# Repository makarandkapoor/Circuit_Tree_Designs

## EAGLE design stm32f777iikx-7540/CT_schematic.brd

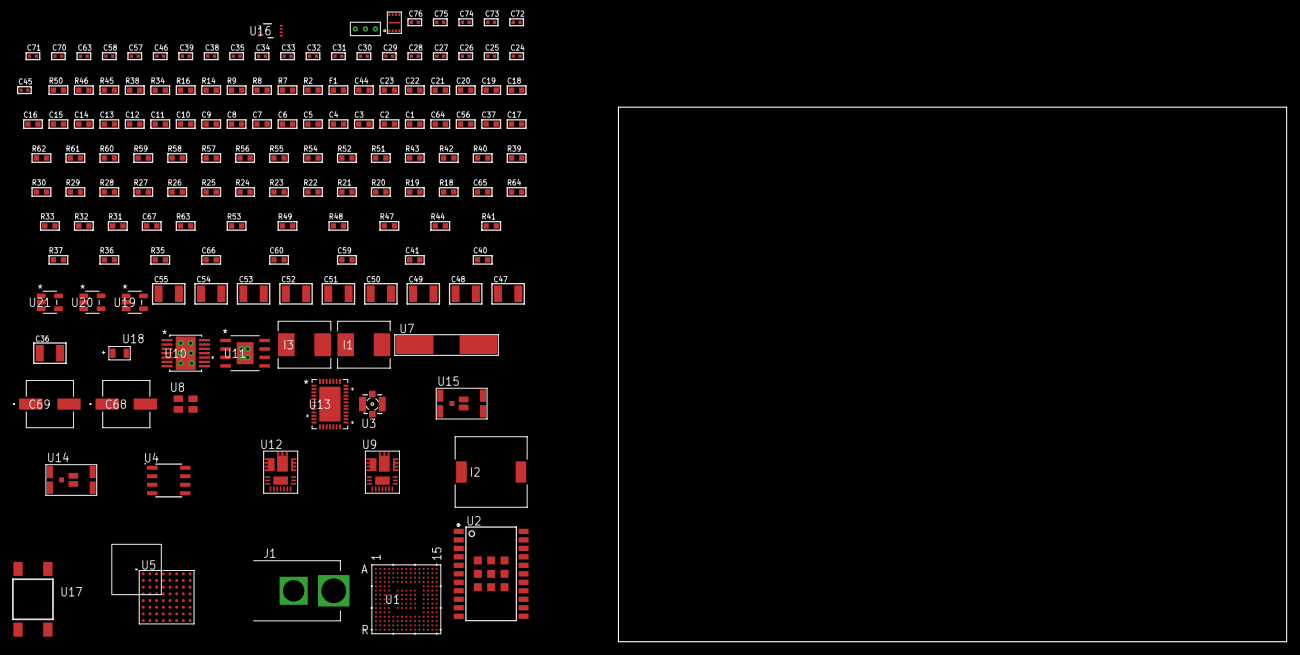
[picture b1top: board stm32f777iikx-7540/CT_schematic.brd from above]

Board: 2 copper layers, 100.0 x 80.0 mm, 152 parts (0 on the bottom side), 86 nets, no tracks yet.

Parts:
C1, C20, C44: 1e-06; C0603
C2, C3, C4, C5, C6, C7, C8, C9, C10, C11, C12, C13, C14, C15, C16, C18, C21, C22, C23: 1e-07; C0603
C17: 4.7e-06; C0603
C19: 1e-08; C0603
C24, C25: 1e-11; C0402
C26, C28, C30, C32, C34, C38, C39, C46, C57, C58, C63, C71, C73: 1e-07; C0402
C27, C29, C31, C33, C35, C70, C72, C74, C75, C76: 1e-08; C0402
C36, C55: 0.0001; C1210
C37, C56, C64: 2.2e-06; C0603
C40, C59: 8.6971073877236e-09; R0603
C41, C60: 2.9649229730876e-07; R0603
C45: 3.3e-09; C0402
C47, C48: 2.2e-05; C1210
C49, C50, C51, C52, C53, C54: 1e-05; C1210
C65: 2.45e-08; R0603
C66: 2.8258362168397e-09; R0603
C67: 7.105e-09; R0603
C68, C69: 0.0001; EXV-9H
F1: 240.0; L0603
I1, I3: 6.8e-07; IND25X25CZ
I2: 7e-06; DR1040
J1: PJ-037B; PJ-037B_PACKAGE
R2: 1000.0; R0603
R7, R8, R9: 4700.0; R0603
R14, R16, R45: 2200.0; R0603
R18, R19, R20, R21, R22, R23, R24, R25, R26, R27, R28, R29, R30, R54, R56, R57, R60, R61, R62: 10000.0; R0603
R31, R32, R33: 100000.0; R0603
R34, R46: 0.1; R0603
R35, R47: 4030.2416170974; R0603
R36, R48: 2878.7440122125; R0603
R37, R49: 58.613333333333; R0603
R38, R50: 130.0; R0603
R39, R51: 39000.0; R0603
R40, R52: 49900.0; R0603
R41, R53: 5147.5789473684; R0603
R42: 30000.0; R0603
R43: 22000.0; R0603
R44: 4031.5447154472; R0603
R55: 75000.0; R0603
R58, R59: 95300.0; R0603
R63: 139872.72727273; R0603
R64: 200000.0; R0603
U1: STM32F777IIK7; UFBGA176_25
U2: A2200-A
U3: 73412-0114; COAXIAL_C
U4: AT24C02D-SSHM-T; AT24C02D
U5: PC28F512P33BFD
U6: SST26WF080BT-104I/NP; USON-8
U7: ABLS-25.000MHZ-B2F-T
U8: ASEK-32.768KHz-ECST; ASEK
U9, U12: IR3899MTR1PBF
U10: tps54225PWP; HTSSOP14
U11: MIC5234YME; SOIC-8_EP
U13: LTC2928CUHF#PBF; QFN-38_UHF
U14, U15: IRF8306MTRPbF; IRF8306MTRPBF
U16: LSF0102DCTR; DCU0008A_N
U17: 4-1437565-2; SW_4-1437565-2
U18: Q65110A2395; LGM67K-G1J2-24-Z
U19, U20, U21: nc7sz125m5x; NC7SZ125M5X
U22: Dummy; DUMMY_PACKAGE_318

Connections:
CLK_CRYSTAL_U1_G1: C24.1, U1.G1, U7.1
CLK_CRYSTAL_U1_H1: C25.1, U1.H1, U7.2
CLK_U1_E1: U1.E1, U8.3
GND: C1.2, C2.2, C3.2, C4.2, C5.2, C6.2, C7.2, C8.2, C9.2, C10.2, C11.2, C12.2, C13.2, C14.2, C15.2, C16.2, C17.2, C18.2, C19.2, C20.2, C21.2, C22.2, C23.2, C24.2, C25.2, C26.2, C27.2, C28.2, C29.2, C30.2, C31.2, C32.2, C33.2, C34.2, C35.2, C37.2, C38.2, C39.2, C44.2, C45.2, C47.2, C48.2, C49.2, C50.2, C51.2, C52.2, C53.2, C54.2, C56.2, C57.2, C58.2, C63.2, C64.2, C65.2, C66.2, C67.2, C68.2, C69.2, C70.2, C71.2, C72.2, C73.2, C74.2, C75.2, C76.2, J1.2, R2.2, R18.2, R22.2, R24.2, R25.2, R34.1, R34.2, R36.2, R39.2, R41.2, R43.2, R45.2, R46.1, R46.2, R48.2, R51.2, R53.2, R55.2, R58.2, R59.2, R60.2, R61.2, R62.2, U1.D5, U1.D7, U1.D8, U1.D9, U1.F2, U1.F6, U1.F7, U1.F8, U1.F9, U1.F10, U1.F12, U1.G2, U1.G6, U1.G7, U1.G8, U1.G9, U1.G10, U1.G12, U1.H6, U1.H7, U1.H8, U1.H9, U1.H10, U1.H12, U1.J6, U1.J7, U1.J8, U1.J9, U1.J10, U1.K6, U1.K7, U1.K8, U1.K9, U1.K10, U1.M1, U1.M8, U1.M9, U1.N1, U2.7, U2.8, U2.23, U2.24, U2.25, U2.26, U2.27, U2.28, U2.29, U2.30, U2.31, U4.4, U5.B2, U5.H2, U5.H4, U5.H6, U6.4, U6.9, U8.2, U9.4, U9.11, U9.17, U10.5, U10.8, U10.9, U10.15, U11.7, U11.EPAD, U12.4, U12.11, U12.17, U13.8, U13.9, U13.10, U13.12, U13.13, U13.24, U13.25, U13.30, U13.32, U13.39, U16.1, U18.C, U19.1, U19.3, U20.1, U20.3, U21.1, U21.3, U22.1
NET_U1_C6: R19.1, U1.C6
NET_U1_D6: R18.1, U1.D6
NET_U1_F13: C23.1, U1.F13
NET_U1_H4: R14.1, U1.H4, U4.6
NET_U1_J1: R9.1, U1.J1, U21.4
NET_U1_J4: R16.1, U1.J4, U4.5
NET_U1_L4: R20.1, U1.L4
NET_U1_R1: C19.1, C20.1, F1.1, U1.P1, U1.R1
NET_U1_R15: U17.3, U17.4
NET_U2_2: R21.2, U2.2
NET_U2_17: R21.1, U2.17
NET_U2_22: R8.1, U2.22, U20.4
NET_U3_1: U2.11, U3.1
NET_U3_2: U2.10, U3.2, U3.3, U3.4
NET_U4_1: R23.1, U4.1
NET_U4_2: R24.1, U4.2
NET_U4_3: R25.1, U4.3
NET_U4_7: R22.1, U4.7
NET_U5_A4: C32.1, C33.1, U5.A4
NET_U5_B4: R27.1, U5.B4
NET_U5_C6: R29.1, U5.C6
NET_U5_D4: R7.1, U5.D4, U19.4
NET_U5_F6: R26.1, U5.F6
NET_U5_F8: R28.1, U5.F8
NET_U5_G8: R30.1, U5.G8
NET_U9_1: C40.1, R35.1, R36.1, R37.1, R38.1, U9.1, U9.8
NET_U9_2: C39.1, U9.2
NET_U9_3: C40.2, C41.1, C41.2, U9.3
NET_U9_5: R39.1, U9.5
NET_U9_10: C37.1, U9.10
NET_U9_12: C36.1, I1.1, U9.12
NET_U9_14: C36.2, U9.14
NET_U9_15: R40.1, R41.1, U9.15
NET_U9_ATNET_3: I1.2, R35.2
NET_U9_ATNET_4: C41.2, R37.2
NET_U10_2: R42.2, R43.1, U10.2
NET_U10_3: C44.1, U10.3
NET_U10_4: C45.1, U10.4
NET_U10_10: C46.1, I2.1, U10.10, U10.11
NET_U10_12: C46.2, U10.12
NET_U11_4: R44.2, R45.1, U11.4
NET_U12_1: C59.1, R47.1, R48.1, R49.1, R50.1, U12.1, U12.8
NET_U12_2: C58.1, U12.2
NET_U12_3: C59.2, C60.1, C60.2, U12.3
NET_U12_5: R51.1, U12.5
NET_U12_10: C56.1, U12.10
NET_U12_12: C55.1, I3.1, U12.12
NET_U12_14: C55.2, U12.14
NET_U12_15: R52.1, R53.1, U12.15
NET_U12_ATNET_3: I3.2, R47.2
NET_U12_ATNET_4: C60.2, R49.2
NET_U13_3: R61.1, U13.3
NET_U13_6: R58.1, U13.6
NET_U13_7: R59.1, U13.7
NET_U13_16: R60.1, R63.1, U13.16
NET_U13_18: R57.1, U13.18
NET_U13_19: R56.1, U13.19, U13.20
NET_U13_21: R54.1, R55.1, U13.21, U19.2, U20.2, U21.2
NET_U13_26: C66.1, U13.26
NET_U13_27: C65.1, U13.27
NET_U13_28: C67.1, U13.28
NET_U13_38: R62.1, U13.38
NET_U14_3: U13.2, U14.3
NET_U15_3: U13.37, U15.3
NET_U16_8: R64.1, U16.8
NET_U17_1: R2.1, U17.1, U17.2
PROC_I2C1_SCL_TOXCVR: U2.15, U16.5
PROC_I2C1_SDA_TOXCVR: U2.16, U16.6
PROC_PE2: U1.A2, U22.3
PROC_PE3: U1.A1, U22.2
PROC_QUADSPI_BK1_IO0: U1.F14, U6.5
PROC_QUADSPI_BK1_IO1: U1.B14, U6.2
PROC_QUADSPI_BK1_IO2: R32.1, U1.K1, U6.3
PROC_QUADSPI_BK1_IO3: R33.1, U1.K2, U6.7
PROC_QUADSPI_BK1_NCS: R31.1, U1.B6, U6.1
PROC_QUADSPI_CLK: U1.L1, U6.6
VCC_16V8: C63.1, C64.1, C68.1, C69.1, J1.1, R54.2, R56.2, R57.2, R63.2, U13.11, U13.22, U14.1, U14.2, U14.6, U14.7, U15.1, U15.2, U15.6, U15.7
VCC_S1_16V8: C38.1, C49.1, C50.1, C51.1, C52.1, R40.2, U9.9, U10.7, U10.13, U10.14, U11.5, U11.8, U14.4, U14.5
VCC_S2_16V8: C57.1, R52.2, U12.9, U15.4, U15.5
VCC_TIER1_1V2: C22.1, I1.2, R35.2, U1.M10
VCC_TIER1_1V8: C1.1, C2.1, C3.1, C4.1, C5.1, C6.1, C7.1, C8.1, C9.1, C10.1, C11.1, C12.1, C13.1, C14.1, C15.1, C16.1, C17.1, C18.1, C27.1, C34.1, C47.1, C48.1, C72.1, C73.1, C74.1, C75.1, C76.1, F1.2, I2.2, R9.2, R14.2, R16.2, R19.2, R20.2, R23.2, R31.2, R32.2, R33.2, R42.1, U1.C1, U1.C5, U1.C7, U1.C8, U1.C9, U1.F3, U1.G3, U1.G13, U1.J12, U1.J13, U1.K4, U1.N8, U1.N9, U1.N10, U4.8, U6.8, U10.1, U16.2, U19.5, U20.5, U21.5
VCC_TIER1_3V3: C21.1, C26.1, C28.1, C29.1, C30.1, C31.1, C35.1, C53.1, C54.1, C70.1, C71.1, R7.2, R8.2, R26.2, R27.2, R28.2, R29.2, R30.2, R44.1, R64.2, U1.H13, U2.20, U5.A6, U5.D5, U5.D6, U5.G4, U5.H3, U8.4, U11.1, U16.7
VCC_TIER2_1V2: I3.2, R47.2

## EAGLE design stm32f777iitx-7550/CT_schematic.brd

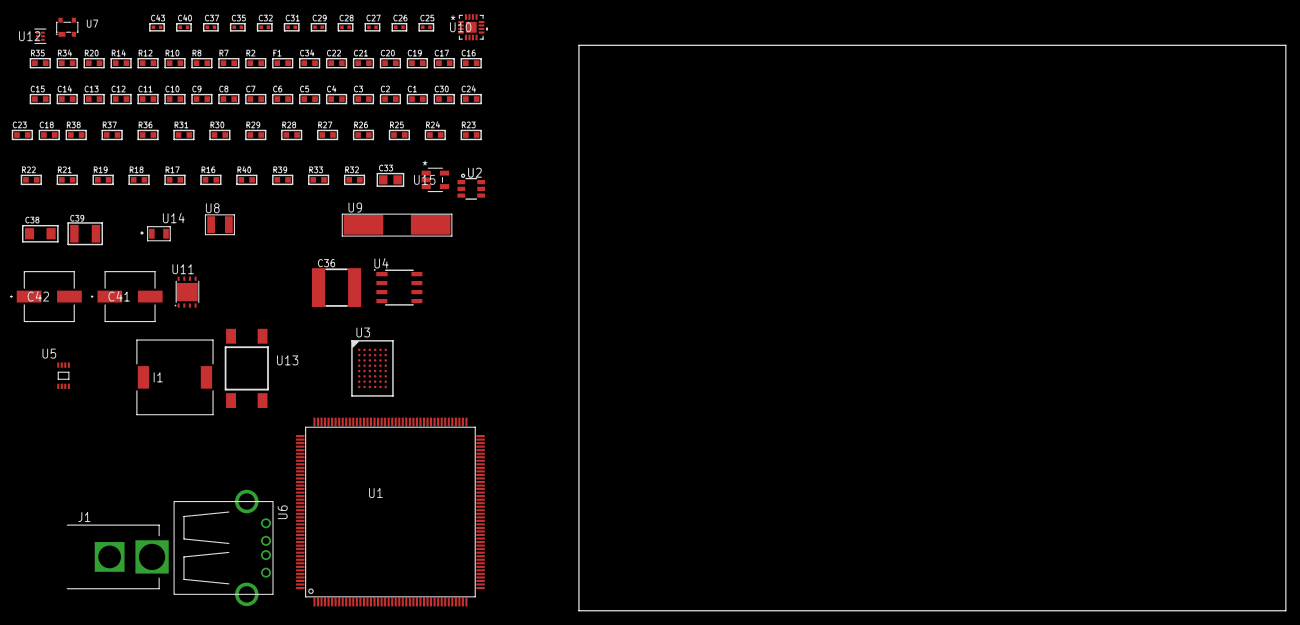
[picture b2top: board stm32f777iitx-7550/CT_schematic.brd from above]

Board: 2 copper layers, 100.0 x 80.0 mm, 92 parts (0 on the bottom side), 82 nets, no tracks yet.

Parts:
C1, C21, C34: 1e-06; C0603
C2, C3, C4, C5, C6, C7, C8, C9, C10, C11, C12, C13, C14, C15, C16, C17, C19, C22: 1e-07; C0603
C18: 4.7e-06; C0603
C20: 1e-08; C0603
C23, C24, C30: 2.2e-06; C0603
C25, C26, C27, C28: 1e-11; C0402
C29, C35, C40: 1e-07; C0402
C31, C32, C37, C43: 1e-08; C0402
C33: 1e-05; C0805
C36: 6.8e-05; 2220
C38: 1e-05; C1206
C39: 1e-05; C1210
C41, C42: 0.0001; EXV-9H
F1: 240.0; L0603
I1: 3.8e-06; DR1040
J1: PJ-037B; PJ-037B_PACKAGE
R2, R35: 1000.0; R0603
R7: 4700.0; R0603
R8, R10, R12, R14: 2200.0; R0603
R16: 47000.0; R0603
R17, R18, R19, R21, R22, R23, R24, R25, R26, R27, R28, R29, R36, R37: 10000.0; R0603
R20: 1270.0; R0603
R30: 20000.0; R0603
R31: 62000.0; R0603
R32: 300000.0; R0603
R33: 100000.0; R0603
R34: 3900.0; R0603
R38: 18000.0; R0603
R39: 470000.0; R0603
R40: 120000.0; R0603
U1: STM32F777IIT6; LQFP176
U2: MAX4995AAUT+T; SOT-23-6
U3: CY62147GE30-45BVXI; VFBGA48
U4: AT24C02D-SSHM-T; AT24C02D
U5: 24AA01T-I/MNY; TDFN-8/6MM
U6: 61400416021; USB-A-H
U7: prtr5v0u2ax; SOT143B
U8: ABS07-32.768KHZ-7-T
U9: ABLS-25.000MHZ-B2F-T
U10: LTC3601EUD#PBF; QFN-16_EP
U11: LP3878SDX-ADJ/NOPB; WSON-8
U12: TPS3895ADRYR; SON-6
U13: 4-1437565-2; SW_4-1437565-2
U14: Q65110A2395; LGM67K-G1J2-24-Z
U15: nc7sz125m5x; NC7SZ125M5X

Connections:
CLK_CRYSTAL_U1_9: C25.1, U1.9, U8.1
CLK_CRYSTAL_U1_10: C26.1, U1.10, U8.2
CLK_CRYSTAL_U1_29: C27.1, U1.29, U9.1
CLK_CRYSTAL_U1_30: C28.1, U1.30, U9.2
GND: C1.2, C2.2, C3.2, C4.2, C5.2, C6.2, C7.2, C8.2, C9.2, C10.2, C11.2, C12.2, C13.2, C14.2, C15.2, C16.2, C17.2, C18.2, C19.2, C20.2, C21.2, C22.2, C23.2, C24.2, C25.2, C26.2, C27.2, C28.2, C29.2, C30.2, C31.2, C32.2, C33.2, C34.2, C36.1, C36.2, C37.2, C38.2, C39.2, C40.2, C41.2, C42.2, C43.2, J1.2, R2.2, R16.2, R17.2, R19.2, R20.2, R22.2, R26.2, R28.2, R29.2, R30.2, R32.2, R35.2, R38.2, R40.2, U1.14, U1.22, U1.37, U1.61, U1.71, U1.90, U1.102, U1.113, U1.126, U1.135, U1.148, U1.158, U2.2, U3.D1, U3.E6, U4.4, U5.4, U6.4, U6.5, U6.6, U7.1, U10.1, U10.9, U10.17, U11.3, U11.PAD, U12.2, U14.C, U15.1, U15.3
NET_U1_31: R7.1, U1.31, U15.4
NET_U1_39: C20.1, C21.1, F1.1, U1.38, U1.39
NET_U1_45: R12.1, U1.45, U5.6
NET_U1_46: R14.1, U1.46, U5.5
NET_U1_48: R19.1, U1.48
NET_U1_81: C23.1, U1.81
NET_U1_121: R20.1, U1.121
NET_U1_125: C24.1, U1.125
NET_U1_164: R8.1, U1.164, U4.6
NET_U1_165: R10.1, U1.165, U4.5
NET_U1_166: R17.1, U1.166
NET_U1_171: R18.1, U1.171
NET_U1_176: U13.3, U13.4
NET_U2_3: R16.1, U2.3
NET_U4_1: R27.1, U4.1
NET_U4_2: R28.1, U4.2
NET_U4_3: R29.1, U4.3
NET_U4_7: R26.1, U4.7
NET_U10_3: C35.2, I1.1, U10.3, U10.4
NET_U10_6: C35.1, U10.6
NET_U10_7: C34.1, U10.7, U10.12
NET_U10_10: R32.1, U10.10
NET_U10_11: R30.1, R31.1, U10.11
NET_U10_ATNET_3: I1.2, R31.2
NET_U11_1: C37.1, U11.1
NET_U11_6: R34.2, R35.1, U11.6
NET_U11_8: R33.1, U11.8
NET_U12_1: R37.1, R38.1, U12.1
NET_U12_3: R39.2, R40.1, U12.3
NET_U12_4: R36.1, U12.4, U15.2
NET_U13_1: R2.1, U13.1, U13.2
PROC_FMC_A0: U1.16, U3.A3
PROC_FMC_A1: U1.17, U3.A4
PROC_FMC_A2: U1.18, U3.A5
PROC_FMC_A3: U1.19, U3.B3
PROC_FMC_A4: U1.20, U3.B4
PROC_FMC_A5: U1.21, U3.C3
PROC_FMC_A6: U1.60, U3.C4
PROC_FMC_A7: U1.63, U3.D4
PROC_FMC_A8: U1.64, U3.H2
PROC_FMC_A9: U1.65, U3.H3
PROC_FMC_A10: U1.66, U3.H4
PROC_FMC_A11: U1.67, U3.H5
PROC_FMC_A12: U1.106, U3.G3
PROC_FMC_A13: U1.107, U3.G4
PROC_FMC_A14: U1.108, U3.F3
PROC_FMC_A15: U1.109, U3.F4
PROC_FMC_A16: U1.99, U3.E4
PROC_FMC_A17: U1.100, U3.D3
PROC_FMC_D0: U1.104, U3.B6
PROC_FMC_D1: U1.105, U3.C5
PROC_FMC_D2: U1.142, U3.C6
PROC_FMC_D3: U1.143, U3.D5
PROC_FMC_D4: U1.68, U3.E5
PROC_FMC_D5: U1.69, U3.F5
PROC_FMC_D6: U1.70, U3.F6
PROC_FMC_D7: U1.73, U3.G6
PROC_FMC_D8: U1.74, U3.B1
PROC_FMC_D9: U1.75, U3.C1
PROC_FMC_D10: U1.76, U3.C2
PROC_FMC_D11: U1.77, U3.D2
PROC_FMC_D12: U1.78, U3.E2
PROC_FMC_D13: U1.96, U3.F2
PROC_FMC_D14: U1.97, U3.F1
PROC_FMC_D15: U1.98, U3.G1
PROC_FMC_NBL0: U1.169, U3.A1
PROC_FMC_NE2: R24.1, U1.117, U3.B5
PROC_FMC_NOE: R23.1, U1.146, U3.A2
PROC_FMC_NWE: R25.1, U1.147, U3.G5
PROC_GPIO_TO_U1_USB_FAULT: R21.1, U1.2, U2.6
PROC_GPIO_TO_U1_VBUS_EN: R22.1, U1.1, U2.4
PROC_USB_OTG_FS_DM: U1.122, U6.2, U7.3
PROC_USB_OTG_FS_DP: U1.123, U6.3, U7.2
PROC_USB_OTG_FS_VBUS: U1.120, U2.1, U6.1, U7.4
VCC_S1_10V1: C33.1, C38.1, C41.1, C42.1, J1.1, R33.2, U10.15, U10.16, U11.4
VCC_TIER1_2V5: C1.1, C2.1, C3.1, C4.1, C5.1, C6.1, C7.1, C8.1, C9.1, C10.1, C11.1, C12.1, C13.1, C14.1, C15.1, C16.1, C17.1, C18.1, C19.1, C22.1, C29.1, C30.1, C31.1, C32.1, C36.2, C40.1, C43.1, F1.2, I1.2, R7.2, R8.2, R10.2, R12.2, R14.2, R18.2, R21.2, R23.2, R24.2, R25.2, R27.2, R31.2, R36.2, R37.2, R39.1, U1.6, U1.15, U1.23, U1.36, U1.49, U1.62, U1.72, U1.82, U1.91, U1.103, U1.114, U1.127, U1.136, U1.149, U1.159, U1.172, U3.D6, U3.E1, U4.8, U5.7, U5.8, U10.8, U12.6, U15.5
VCC_TIER1_5V0: C39.1, R34.1, U2.5, U11.5

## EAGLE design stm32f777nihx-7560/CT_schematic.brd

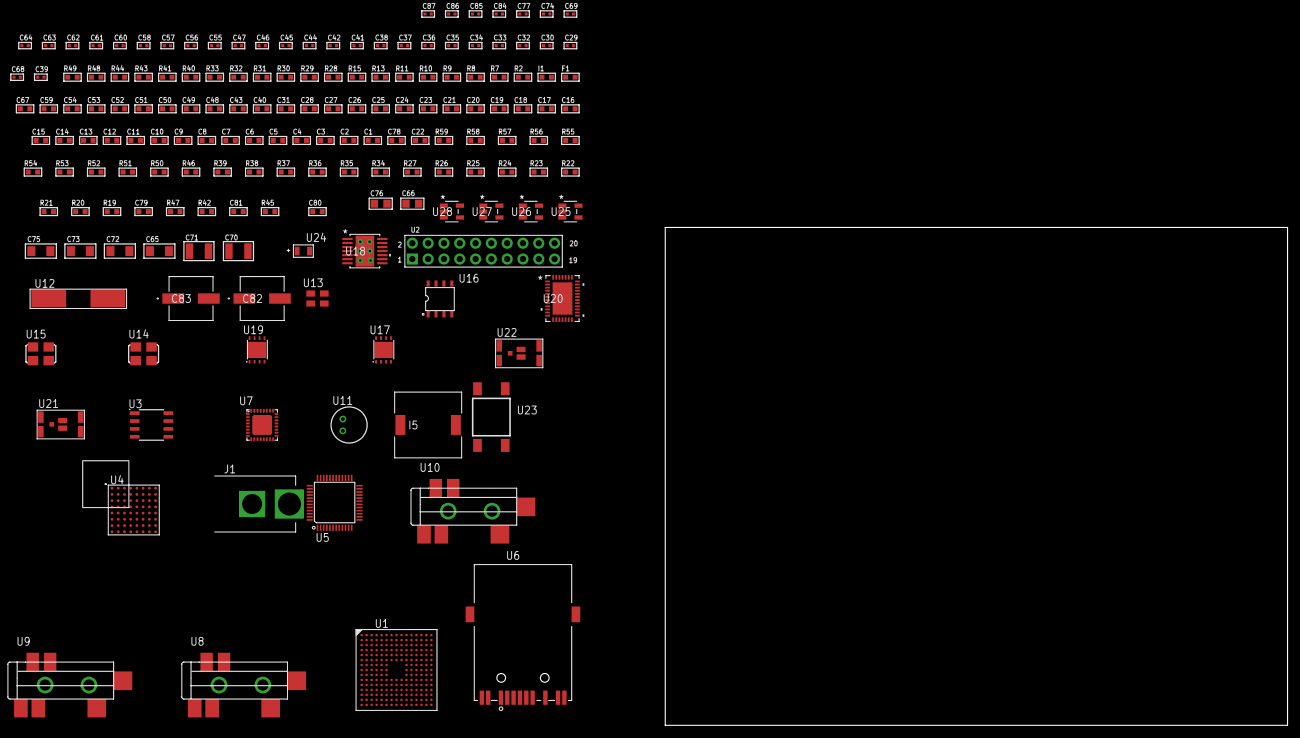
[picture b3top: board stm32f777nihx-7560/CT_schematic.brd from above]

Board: 2 copper layers, 100.0 x 80.0 mm, 168 parts (0 on the bottom side), 161 nets, no tracks yet.

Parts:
C1, C25, C31, C40, C43, C48, C49, C50, C51, C52, C53, C54, C59, C67: 1e-06; C0603
C2, C3, C4, C5, C6, C7, C8, C9, C10, C11, C12, C13, C14, C15, C16, C17, C18, C19, C20, C21, C23, C26, C27, C28: 1e-07; C0603
C22: 4.7e-06; C0603
C24: 1e-08; C0603
C29, C30: 1e-11; C0402
C32, C34, C36, C38, C42, C45, C60, C61, C62, C63, C64, C74, C84, C85, C86, C87: 1e-08; C0402
C33, C35, C37, C41, C44, C46, C47, C55, C56, C57, C58, C69, C77: 1e-07; C0402
C39: 2.2e-08; C0402
C65, C72, C73, C75: 1e-05; C1206
C66, C76: 1e-05; C0805
C68: 3.3e-09; C0402
C70, C71: 2.2e-05; C1210
C78: 2.2e-06; C0603
C79: 2.45e-08; R0603
C80: 2.8258362168397e-09; R0603
C81: 7.105e-09; R0603
C82, C83: 0.0001; EXV-9H
F1: 240.0; L0603
I1: 97.0; R0603
I5: 2.5e-06; DR1040
J1: PJ-037B; PJ-037B_PACKAGE
R2, R44, R49: 1000.0; R0603
R7, R8, R9, R10, R33: 4700.0; R0603
R11, R13, R15: 2200.0; R0603
R19, R20, R21, R22, R23, R24, R25, R26, R27, R34, R35, R36, R37, R38, R39, R50, R52, R53, R56, R57, R58: 10000.0; R0603
R28, R29: 0.1; R0603
R30, R31, R43, R48: 200.0; R0603
R32: 2490.0; R0603
R40, R41: 1270.0; R0603
R42, R47: 100000.0; R0603
R45: 71007.101651032; R0603
R46: 22000.0; R0603
R51: 75000.0; R0603
R54, R55: 95300.0; R0603
R59: 82000.0; R0603
U1: STM32F777NIH6; TFBGA216
U2: arducam_ov2640; ARDUCAM
U3: M24M02-DRMN6TP; SOIC-8
U4: PC28F512P33BFD
U5: RTL8201FL-VB-CG
U6: 7498011122R
U7: SGTL5000XNAA3; QFN-32
U8, U9, U10: SJ-43515TS-SMT-TR
U11: WM-64PCT; WM-64PC
U12: ABLS-25.000MHZ-B2F-T
U13: ASEK-32.768KHz-ECST; ASEK
U14: ASFL-24.57MHZ-NCS; ASFL1
U15: ASFL1-25MHZ-NCS; ASFL1
U16: idt74fct38072; IDT74FCT38072
U17, U19: LP3878SDX-ADJ/NOPB; WSON-8
U18: tps54525PWP; HTSSOP14
U20: LTC2928CUHF#PBF; QFN-38_UHF
U21, U22: IRF8306MTRPbF; IRF8306MTRPBF
U23: 4-1437565-2; SW_4-1437565-2
U24: Q65110A2395; LGM67K-G1J2-24-Z
U25, U26, U27, U28: nc7sz125m5x; NC7SZ125M5X

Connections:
CLK_CRYSTAL_U1_G1: C29.1, U1.G1, U12.1
CLK_CRYSTAL_U1_H1: C30.1, U1.H1, U12.2
CLK_U1_E1: U1.E1, U13.3
CLK_U2_8: U2.8, U16.7
CLK_U5_43: U5.43, U16.6
CLK_U7_21: U7.21, U14.3
CLK_U16_3: U15.3, U16.3
GND: C1.2, C2.2, C3.2, C4.2, C5.2, C6.2, C7.2, C8.2, C9.2, C10.2, C11.2, C12.2, C13.2, C14.2, C15.2, C16.2, C17.2, C18.2, C19.2, C20.2, C21.2, C22.2, C23.2, C24.2, C25.2, C26.2, C27.2, C28.2, C29.2, C30.2, C31.2, C32.2, C33.2, C34.2, C35.2, C36.2, C37.2, C38.2, C39.2, C40.2, C41.2, C42.2, C43.2, C44.2, C45.2, C46.2, C47.2, C55.2, C56.2, C57.2, C58.2, C59.2, C60.2, C61.2, C62.2, C63.2, C64.2, C65.2, C66.2, C67.2, C68.2, C70.2, C71.2, C72.2, C73.2, C74.2, C75.2, C76.2, C77.2, C78.2, C79.2, C80.2, C81.2, C82.2, C83.2, C84.2, C85.2, C86.2, C87.2, J1.2, R2.2, R19.2, R22.2, R28.2, R29.2, R32.2, R34.2, R35.2, R37.2, R39.2, R41.2, R44.2, R46.2, R49.2, R51.2, R54.2, R55.2, R56.2, R57.2, R58.2, U1.F2, U1.F6, U1.F7, U1.F8, U1.F9, U1.F10, U1.G6, U1.G10, U1.H6, U1.H10, U1.J6, U1.J10, U1.K6, U1.K7, U1.K8, U1.K9, U1.K10, U1.L6, U1.M1, U1.N1, U2.2, U2.20, U3.4, U4.B2, U4.H2, U4.H4, U4.H6, U5.7, U5.20, U5.33, U5.42, U5.47, U6.9, U7.1, U7.3, U7.7, U7.EXP, U9.1, U10.1, U11.2, U13.2, U14.2, U15.2, U16.4, U16.5, U16.8, U17.3, U17.PAD, U18.5, U18.8, U18.9, U18.15, U19.3, U19.PAD, U20.8, U20.9, U20.10, U20.12, U20.13, U20.24, U20.25, U20.30, U20.32, U20.39, U24.C, U25.1, U25.3, U26.1, U26.3, U27.1, U27.3, U28.1, U28.3
NET_U1_B4: R13.1, U1.B4, U3.5
NET_U1_B6: R11.1, U1.B6, U3.6
NET_U1_E5: R20.1, U1.E5
NET_U1_E6: R19.1, U1.E6
NET_U1_E11: C28.1, U1.E11
NET_U1_J1: R9.1, U1.J1, U27.4
NET_U1_L5: R21.1, U1.L5
NET_U1_M3: R15.1, U1.M3, U5.30
NET_U1_R1: C24.1, C25.1, F1.1, U1.P1, U1.R1
NET_U1_R15: U23.3, U23.4
NET_U2_19: R10.1, U2.19, U28.4
NET_U3_3: R22.1, U3.3
NET_U4_A4: C37.1, C38.1, U4.A4
NET_U4_C6: R26.1, U4.C6
NET_U4_D4: R8.1, U4.D4, U26.4
NET_U5_6: C40.1, C41.1, C42.1, I1.1, U5.6, U5.41
NET_U5_10: R37.1, U5.10
NET_U5_29: R7.1, U5.29, U25.4
NET_U5_32: R33.1, U5.32
NET_U5_34: R35.1, U5.34
NET_U5_35: R36.1, U5.35
NET_U5_40: C47.1, U5.40
NET_U5_46: R32.1, U5.46
NET_U5_48: C46.1, U5.48
NET_U6_1: U5.1, U6.1
NET_U6_3: U5.2, U6.3
NET_U6_4: U5.4, U6.4
NET_U6_5: C39.1, U6.2, U6.5
NET_U6_6: U5.5, U6.6
NET_U6_8: R29.1, U6.8
NET_U6_10: R30.1, U6.10
NET_U6_12: R31.1, U6.12
NET_U6_13: R28.1, U6.13, U6.14
NET_U7_10: C58.1, U7.10
NET_U7_29: R40.1, U7.29
NET_U7_31: R41.1, U7.31
NET_U8_1: U7.4, U8.1
NET_U8_2: U7.2, U8.2
NET_U8_5: U7.6, U8.5
NET_U9_2: C49.1, U9.2
NET_U9_5: C48.1, U9.5
NET_U10_2: C51.1, C52.1, U10.2
NET_U10_5: C50.1, U10.5
NET_U10_13: C51.2, C52.2
NET_U11_1: C53.1, C54.1, C59.1, U7.16, U11.1
NET_U11_15: C53.2, C54.2
NET_U17_1: C64.1, U17.1
NET_U17_6: R43.2, R44.1, U17.6
NET_U17_8: R42.1, U17.8
NET_U18_2: R45.2, R46.1, U18.2
NET_U18_3: C67.1, U18.3
NET_U18_4: C68.1, U18.4
NET_U18_10: C69.1, I5.1, U18.10, U18.11
NET_U18_12: C69.2, U18.12
NET_U19_1: C74.1, U19.1
NET_U19_6: R48.2, R49.1, U19.6
NET_U19_8: R47.1, U19.8
NET_U20_3: R57.1, U20.3
NET_U20_6: R54.1, U20.6
NET_U20_7: R55.1, U20.7
NET_U20_16: R56.1, R59.1, U20.16
NET_U20_18: R53.1, U20.18
NET_U20_19: R52.1, U20.19, U20.20
NET_U20_21: R50.1, R51.1, U20.21, U25.2, U26.2, U27.2, U28.2
NET_U20_22: C77.1, R50.2, R52.2, R53.2, U20.11, U20.22
NET_U20_26: C80.1, U20.26
NET_U20_27: C79.1, U20.27
NET_U20_28: C81.1, U20.28
NET_U20_38: R58.1, U20.38
NET_U21_3: U20.2, U21.3
NET_U22_3: U20.37, U22.3
NET_U23_1: R2.1, U23.1, U23.2
PROC_DCMI_D0: U1.E15, U2.18
PROC_DCMI_D1: U1.D15, U2.17
PROC_DCMI_D2: U1.A6, U2.16
PROC_DCMI_D3: U1.A5, U2.15
PROC_DCMI_D4: U1.B13, U2.14
PROC_DCMI_D5: U1.C3, U2.13
PROC_DCMI_D6: U1.D6, U2.12
PROC_DCMI_D7: U1.D4, U2.11
PROC_DCMI_D8: U1.B14, U2.10
PROC_DCMI_D9: U1.A12, U2.9
PROC_DCMI_HSYNC: U1.N4, U2.6
PROC_DCMI_PIXCLK: U1.P3, U2.7
PROC_DCMI_VSYNC: U1.D3, U2.5
PROC_ETH_COL: U1.J4, U5.38
PROC_ETH_CRS: U1.K4, U5.36
PROC_ETH_RXD3: R38.1, U1.N13, U5.18
PROC_ETH_RX_CLK: U1.N2, U5.19
PROC_ETH_RX_DV: R34.1, U5.13
PROC_ETH_RX_ER: R39.1, U1.D5, U5.39
PROC_ETH_TXD0: U1.L13, U5.23
PROC_ETH_TXD1: U1.A4, U5.24
PROC_ETH_TXD2: U1.M4, U5.25
PROC_ETH_TXD3: U1.A7, U5.26
PROC_ETH_TX_CLK: U1.L4, U5.22
PROC_ETH_TX_EN: U1.B8, U5.27
PROC_FMC_A0: U1.D2, U4.A1
PROC_FMC_A1: U1.E2, U4.B1
PROC_FMC_A2: U1.G2, U4.C1
PROC_FMC_A3: U1.H2, U4.D1
PROC_FMC_A4: U1.J2, U4.D2
PROC_FMC_A5: U1.K3, U4.A2
PROC_FMC_A6: U1.M6, U4.C2
PROC_FMC_A7: U1.N6, U4.A3
PROC_FMC_A8: U1.P6, U4.B3
PROC_FMC_A9: U1.M8, U4.C3
PROC_FMC_A10: U1.N7, U4.D3
PROC_FMC_A11: U1.M7, U4.C4
PROC_FMC_A12: U1.M13, U4.A5
PROC_FMC_A13: U1.M12, U4.B5
PROC_FMC_A14: U1.N12, U4.C5
PROC_FMC_A15: U1.N11, U4.D7
PROC_FMC_A16: U1.N10, U4.D8
PROC_FMC_A17: U1.M10, U4.A7
PROC_FMC_A18: U1.M11, U4.B7
PROC_FMC_A19: U1.A2, U4.C7
PROC_FMC_A20: U1.A1, U4.C8
PROC_FMC_A21: U1.B1, U4.A8
PROC_FMC_A22: U1.B2, U4.G1
PROC_FMC_A23: U1.A3, U4.H8
PROC_FMC_A24: U1.B3, U4.B6
PROC_FMC_CLK: U1.C11, U4.E6
PROC_FMC_D0: U1.L12, U4.F2
PROC_FMC_D1: U1.K13, U4.E2
PROC_FMC_D2: U1.B12, U4.G3
PROC_FMC_D3: U1.C12, U4.E4
PROC_FMC_D4: U1.R8, U4.E5
PROC_FMC_D5: U1.N9, U4.G5
PROC_FMC_D6: U1.P9, U4.G6
PROC_FMC_D7: U1.R9, U4.H7
PROC_FMC_D8: U1.P10, U4.E1
PROC_FMC_D9: U1.R10, U4.E3
PROC_FMC_D10: U1.R12, U4.F3
PROC_FMC_D11: U1.P11, U4.F4
PROC_FMC_D12: U1.R11, U4.F5
PROC_FMC_D13: U1.L15, U4.H5
PROC_FMC_D14: U1.L14, U4.G7
PROC_FMC_D15: U1.K15, U4.E7
PROC_FMC_NE2: R24.1, U1.D9, U4.B4
PROC_FMC_NL: R23.1, U1.B5, U4.F6
PROC_FMC_NOE: R25.1, U1.D11, U4.F8
PROC_FMC_NWAIT: U1.B11, U4.F7
PROC_FMC_NWE: R27.1, U1.C10, U4.G8
PROC_I2S1_CK: U1.A10, U7.24
PROC_I2S1_SD: U1.A8, U7.26
PROC_I2S1_WS: U1.A13, U7.23
VCC_10V1: C78.1, C82.1, C83.1, J1.1, R59.2, U20.23, U21.1, U21.2, U21.6, U21.7, U22.1, U22.2, U22.6, U22.7
VCC_S1_10V1: C65.1, C72.1, C73.1, R42.2, U17.4, U18.7, U18.13, U18.14, U21.4, U21.5
VCC_S2_10V1: C75.1, R47.2, U19.4, U22.4, U22.5
VCC_TIER1_1V2: C27.1, C55.1, C66.1, R43.1, U1.L11, U7.30, U17.5
VCC_TIER1_3V3: C1.1, C2.1, C3.1, C4.1, C5.1, C6.1, C7.1, C8.1, C9.1, C10.1, C11.1, C12.1, C13.1, C14.1, C15.1, C16.1, C17.1, C18.1, C19.1, C20.1, C21.1, C22.1, C23.1, C26.1, C31.1, C32.1, C33.1, C34.1, C35.1, C36.1, C43.1, C44.1, C45.1, C56.1, C57.1, C60.1, C61.1, C62.1, C63.1, C70.1, C71.1, C84.1, C85.1, C86.1, C87.1, F1.2, I1.2, I5.2, R7.2, R8.2, R9.2, R10.2, R11.2, R13.2, R15.2, R20.2, R21.2, R23.2, R24.2, R25.2, R26.2, R27.2, R33.2, R36.2, R38.2, R40.2, R45.1, U1.C1, U1.E7, U1.E8, U1.E9, U1.E10, U1.F4, U1.F5, U1.F11, U1.G5, U1.G11, U1.H5, U1.H11, U1.J5, U1.J11, U1.K5, U1.K11, U1.L7, U1.L8, U1.L9, U1.L10, U2.1, U3.8, U4.A6, U4.D5, U4.D6, U4.G4, U4.H3, U5.15, U5.21, U5.37, U7.5, U7.20, U13.4, U14.4, U15.4, U16.1, U16.2, U18.1, U25.5, U26.5, U27.5, U28.5
VCC_TIER2_1V2: C76.1, R48.1, U19.5

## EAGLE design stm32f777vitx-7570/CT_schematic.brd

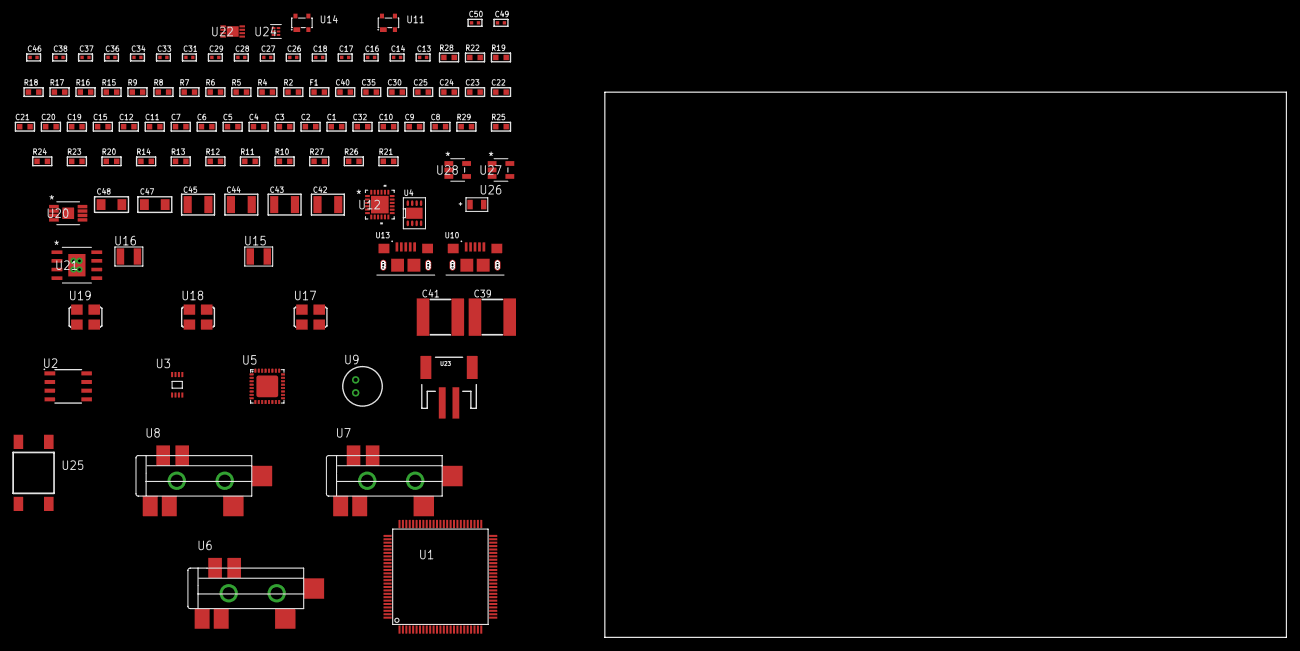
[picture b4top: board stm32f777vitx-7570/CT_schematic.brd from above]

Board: 2 copper layers, 106 parts (0 on the bottom side), 73 nets, no tracks yet.

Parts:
C1, C12, C15, C19, C20, C21, C22, C23, C24, C25, C30, C35, C40: 1e-06; C0603
C2, C3, C4, C5, C6, C7: 1e-07; C0603
C8: 4.7e-06; C0603
C9, C10, C32: 2.2e-06; C0603
C11: 1e-08; C0603
C13, C14: 1e-11; C0402
C16, C17, C31, C33, C34, C36, C37, C38, C49, C50: 1e-08; C0402
C18, C26, C27, C28, C29, C46: 1e-07; C0402
C39, C41: 6.8e-05; 2220
C42, C43, C44, C45: 1e-05; C1210
C47, C48: 1e-05; C1206
F1: 240.0; L0603
R2: 1000.0; R0603
R4, R5: 4700.0; R0603
R6, R7, R8, R9, R19, R22: 2200.0; R0603
R10, R11, R12, R13, R14, R20, R23, R24, R29: 10000.0; R0603
R15, R16: 1270.0; R0603
R17: 8060.0; R0603
R18: 3900.0; R0603
R21: 4031.5447154472; R0603
R25: 82000.0; R0603
R26: 300000.0; R0603
R27: 120000.0; R0603
R28: 2000.0; R0603
U1: STM32F777VIT6; LQFP100
U2: AT25040B-SSHL-T; SOIC-8
U3: 24AA04-I/MC; TDFN-8/6MM
U4: PCF85063TP/1Z; SON-8
U5: SGTL5000XNAA3; QFN-32
U6, U7, U8: SJ-43515TS-SMT-TR
U9: WM-64PCT; WM-64PC
U10, U13: 10118193-0001LF; FCI_10118193-0001LF
U11, U14: prtr5v0u2ax; SOT143B
U12: USB3317C-CP-TR; QFN-24
U15, U16: ABS07-32.768KHZ-7-T
U17: ASFL-24.57MHZ-NCS; ASFL1
U18: ASFL1-25MHZ-NCS; ASFL1
U19: ASFL1-26MHZ-NCS; ASFL1
U20: MIC47100YMME; MSOP-8_EP
U21: MIC5234YME; SOIC-8_EP
U22: MCP73831T-2ACI/MC; DFN8_2X3MC
U23: S2B-PH-SM4-TB(LF)(SN); JST-2-SMD
U24: TPS3895ADRYR; SON-6
U25: 4-1437565-2; SW_4-1437565-2
U26: Q65110A2395; LGM67K-G1J2-24-Z
U27, U28: nc7sz125m5x; NC7SZ125M5X

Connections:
CLK_CRYSTAL_U1_8: C13.1, U1.8, U16.1
CLK_CRYSTAL_U1_9: C14.1, U1.9, U16.2
CLK_CRYSTAL_U4_1: U4.1, U15.1
CLK_CRYSTAL_U4_2: U4.2, U15.2
CLK_U1_12: U1.12, U18.3
CLK_U5_21: U5.21, U17.3
CLK_U12_23: U12.23, U19.3
GND: C1.2, C2.2, C3.2, C4.2, C5.2, C6.2, C7.2, C8.2, C9.2, C10.2, C11.2, C12.2, C13.2, C14.2, C15.2, C16.2, C17.2, C18.2, C26.2, C27.2, C28.2, C29.2, C30.2, C31.2, C32.2, C33.2, C34.2, C35.2, C36.2, C37.2, C38.2, C39.2, C40.2, C41.2, C42.2, C43.2, C44.2, C45.2, C46.2, C47.2, C48.2, C49.2, C50.2, R2.2, R10.2, R16.2, R17.2, R19.2, R22.2, R25.2, R27.2, R28.2, U1.10, U1.19, U1.26, U1.49, U1.70, U1.74, U1.99, U2.4, U3.4, U4.4, U4.PAD, U5.1, U5.3, U5.7, U5.EXP, U7.1, U8.1, U9.2, U10.5, U10.6, U10.7, U10.8, U10.9, U11.1, U12.25, U13.5, U13.6, U13.7, U13.8, U13.9, U14.1, U17.2, U18.2, U19.2, U20.3, U20.EPAD, U21.7, U21.EPAD, U22.6, U22.9, U23.2, U24.2, U26.C, U27.1, U27.3, U28.1, U28.3
INPUT_USBPOWER_5V: C15.1, C47.1, R29.2, U1.68, U10.1, U11.4, U22.1, U22.2
NET_U1_14: R4.1, U1.14, U27.4
NET_U1_21: C11.1, C12.1, F1.1, U1.20, U1.21
NET_U1_48: C9.1, U1.48
NET_U1_66: R9.1, U1.66, U3.5
NET_U1_67: R8.1, U1.67, U3.6
NET_U1_73: C10.1, U1.73
NET_U1_92: R6.1, U1.92, U4.6
NET_U1_93: R7.1, U1.93, U4.5
NET_U1_94: R10.1, U1.94
NET_U1_98: U25.3, U25.4
NET_U2_3: R11.1, U2.3
NET_U2_7: R13.1, U2.7
NET_U4_3: R14.1, U4.3
NET_U5_10: C29.1, U5.10
NET_U5_29: R15.1, U5.29
NET_U5_31: R16.1, U5.31
NET_U6_1: U5.4, U6.1
NET_U6_2: U5.2, U6.2
NET_U6_5: U5.6, U6.5
NET_U7_2: C20.1, U7.2
NET_U7_5: C19.1, U7.5
NET_U8_2: C22.1, C23.1, U8.2
NET_U8_5: C21.1, U8.5
NET_U8_13: C22.2, C23.2
NET_U9_1: C24.1, C25.1, C30.1, U5.16, U9.1
NET_U9_15: C24.2, C25.2
NET_U12_4: C32.1, U12.4
NET_U12_22: R5.1, U12.22, U28.4
NET_U12_24: R17.1, U12.24
NET_U13_1: C35.1, U12.2, U13.1, U14.4
NET_U13_2: U12.5, U13.2, U14.3
NET_U13_3: U12.6, U13.3, U14.2
NET_U20_6: R18.2, R19.1, U20.6
NET_U21_4: R21.2, R22.1, U21.4
NET_U22_5: R29.1, U22.5
NET_U22_8: R28.1, U22.8
NET_U24_1: R24.1, R25.1, U24.1
NET_U24_3: R26.2, R27.1, U24.3
NET_U24_4: R23.1, U24.4, U27.2, U28.2
NET_U25_1: R2.1, U25.1, U25.2
PROC_I2S2_CK: U1.84, U5.24
PROC_I2S2_SD: U1.16, U5.26
PROC_I2S2_WS: U1.90, U5.23
PROC_SPI1_MISO: U1.30, U2.2
PROC_SPI1_MOSI: U1.31, U2.5
PROC_SPI1_NSS: R12.1, U1.28, U2.1
PROC_SPI1_SCK: U1.89, U2.6
PROC_USB_OTG_FS_DM: U1.70, U10.2, U11.3
PROC_USB_OTG_FS_DP: U1.71, U10.3, U11.2
PROC_USB_OTG_HS_ULPI_CK: U1.29, U12.12
PROC_USB_OTG_HS_ULPI_D0: U1.25, U12.16
PROC_USB_OTG_HS_ULPI_D1: U1.34, U12.15
PROC_USB_OTG_HS_ULPI_D2: U1.35, U12.14
PROC_USB_OTG_HS_ULPI_D3: U1.46, U12.13
PROC_USB_OTG_HS_ULPI_D4: U1.47, U12.11
PROC_USB_OTG_HS_ULPI_D5: U1.51, U12.10
PROC_USB_OTG_HS_ULPI_D6: U1.52, U12.9
PROC_USB_OTG_HS_ULPI_D7: U1.91, U12.8
PROC_USB_OTG_HS_ULPI_DIR: U1.17, U12.19
PROC_USB_OTG_HS_ULPI_NXT: U1.18, U12.18
PROC_USB_OTG_HS_ULPI_STP: U1.15, U12.20
VCC_S1_3V7: C39.1, C40.1, C42.1, C43.1, C48.1, R20.1, R20.2, U20.1, U20.2, U20.4, U20.5, U21.5, U21.8, U22.3, U22.4, U23.1
VCC_TIER1_1V8: C1.1, C2.1, C3.1, C4.1, C5.1, C6.1, C7.1, C8.1, C16.1, C17.1, C18.1, C26.1, C27.1, C28.1, C33.1, C34.1, C41.1, C46.1, C49.1, C50.1, F1.2, R4.2, R5.2, R6.2, R7.2, R8.2, R9.2, R11.2, R12.2, R13.2, R14.2, R15.2, R18.1, R23.2, R24.2, R26.1, U1.6, U1.11, U1.27, U1.50, U1.75, U1.100, U2.8, U3.7, U3.8, U4.8, U5.5, U5.20, U5.30, U12.17, U12.21, U20.7, U20.8, U24.6, U27.5, U28.5
VCC_TIER1_3V3: C31.1, C36.1, C37.1, C38.1, C44.1, C45.1, R21.1, U12.3, U17.4, U18.4, U19.4, U21.1

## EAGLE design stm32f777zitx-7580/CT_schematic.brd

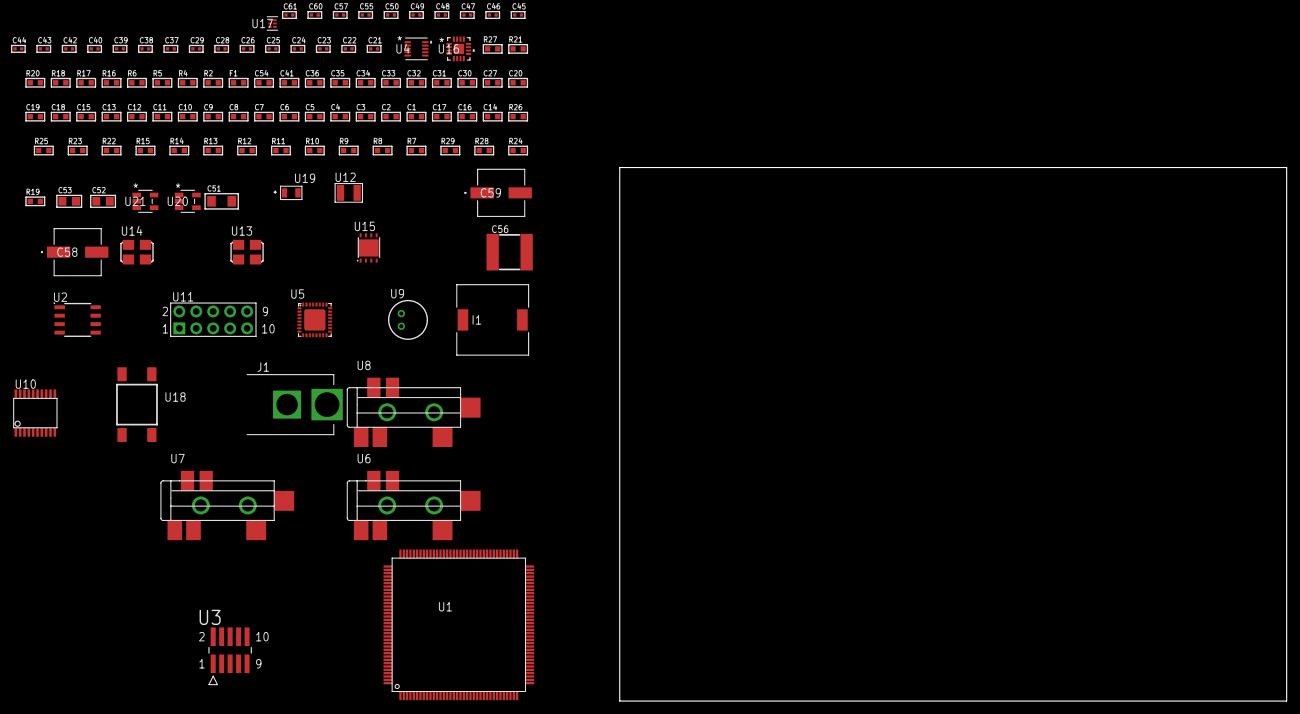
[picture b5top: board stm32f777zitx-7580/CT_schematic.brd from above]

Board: 2 copper layers, 100.0 x 80.0 mm, 112 parts (0 on the bottom side), 74 nets, no tracks yet.

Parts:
C1, C19, C27, C30, C31, C32, C33, C34, C35, C36, C41, C54: 1e-06; C0603
C2, C3, C4, C5, C6, C7, C8, C9, C10, C11, C12, C13, C15, C20: 1e-07; C0603
C14: 4.7e-06; C0603
C16, C17: 2.2e-06; C0603
C18: 1e-08; C0603
C21, C22: 1e-11; C0402
C23, C48, C49, C50, C60, C61: 1e-08; C0402
C24, C25, C26, C28, C29, C37, C38, C39, C40, C42, C43, C44, C45, C46, C47, C55, C57: 1e-07; C0402
C51: 1e-05; C1206
C52, C53: 1e-05; C0805
C56: 6.8e-05; 2220
C58, C59: 0.0001; EXV-9H
F1: 240.0; L0603
I1: 5.2e-06; DR1040
J1: PJ-037B; PJ-037B_PACKAGE
R2, R21: 1000.0; R0603
R4: 4700.0; R0603
R5, R6: 2200.0; R0603
R7, R8, R9, R10, R11, R12, R13, R14, R15, R25, R26: 10000.0; R0603
R16: 5.0; R0603
R17, R18: 1270.0; R0603
R19: 100000.0; R0603
R20: 200.0; R0603
R22: 20000.0; R0603
R23: 91000.0; R0603
R24: 300000.0; R0603
R27: 9100.0; R0603
R28: 680000.0; R0603
R29: 120000.0; R0603
U1: STM32F777ZIT6; LQFP144
U2: AT25020B-SSHL-T; SOIC-8
U3: FTSH-105-01-L-DV-K; SAMTEC_FTSH-105-01-L-DV-K
U4: MAG3110FCR1; DFN-10
U5: SGTL5000XNAA3; QFN-32
U6, U7, U8: SJ-43515TS-SMT-TR
U9: WM-64PCT; WM-64PC
U10: SP3203ECY-L/TR; TSSOP20-I
U11: HTSS-105-01-G-D
U12: ABS07-32.768KHZ-7-T
U13: ASFL-24.57MHZ-NCS; ASFL1
U14: ASFL1-25MHZ-NCS; ASFL1
U15: LP3878SDX-ADJ/NOPB; WSON-8
U16: LTC3601EUD#PBF; QFN-16_EP
U17: TPS3895ADRYR; SON-6
U18: 4-1437565-2; SW_4-1437565-2
U19: Q65110A2395; LGM67K-G1J2-24-Z
U20, U21: nc7sz125m5x; NC7SZ125M5X

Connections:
CLK_CRYSTAL_U1_8: C21.1, U1.8, U12.1
CLK_CRYSTAL_U1_9: C22.1, U1.9, U12.2
CLK_U1_23: U1.23, U14.3
CLK_U5_21: U5.21, U13.3
GND: C1.2, C2.2, C3.2, C4.2, C5.2, C6.2, C7.2, C8.2, C9.2, C10.2, C11.2, C12.2, C13.2, C14.2, C15.2, C16.2, C17.2, C18.2, C19.2, C20.2, C21.2, C22.2, C23.2, C24.2, C25.2, C26.2, C27.2, C28.2, C29.2, C37.2, C38.2, C39.2, C40.2, C41.2, C42.2, C43.2, C46.2, C47.2, C48.2, C49.2, C50.2, C51.2, C52.2, C53.2, C54.2, C56.1, C56.2, C57.2, C58.2, C59.2, C60.2, C61.2, J1.2, R2.2, R7.2, R15.2, R16.2, R18.2, R21.2, R22.2, R24.2, R27.2, R29.2, U1.16, U1.31, U1.38, U1.51, U1.61, U1.83, U1.94, U1.107, U1.120, U1.130, U2.4, U3.3, U3.5, U4.5, U4.10, U5.1, U5.3, U5.7, U5.EXP, U7.1, U8.1, U9.2, U10.18, U11.9, U13.2, U14.2, U15.3, U15.PAD, U16.1, U16.9, U16.17, U17.2, U19.C, U20.2, U20.3, U21.1, U21.3
NET_U1_25: R4.1, U1.25, U21.4
NET_U1_33: C18.1, C19.1, F1.1, U1.32, U1.33
NET_U1_71: C16.1, U1.71
NET_U1_106: C17.1, U1.106
NET_U1_136: R5.1, U1.136, U4.7
NET_U1_137: R6.1, U1.137, U4.6
NET_U1_138: R7.1, U1.138
NET_U1_142: U18.3, U18.4
NET_U1_143: R8.1, U1.143
NET_U2_3: R9.1, U2.3
NET_U2_7: R11.1, U2.7
NET_U3_9: R16.1, U3.9
NET_U4_1: C25.1, U4.1
NET_U4_4: C28.1, U4.4
NET_U5_10: C40.1, U5.10
NET_U5_29: R17.1, U5.29
NET_U5_31: R18.1, U5.31
NET_U6_1: U5.4, U6.1
NET_U6_2: U5.2, U6.2
NET_U6_5: U5.6, U6.5
NET_U7_2: C31.1, U7.2
NET_U7_5: C30.1, U7.5
NET_U8_2: C33.1, C34.1, U8.2
NET_U8_5: C32.1, U8.5
NET_U8_13: C33.2, C34.2
NET_U9_1: C35.1, C36.1, C41.1, U5.16, U9.1
NET_U9_15: C35.2, C36.2
NET_U10_1: C44.1, U10.1
NET_U10_2: C46.1, U10.2
NET_U10_3: C44.2, U10.3
NET_U10_4: C45.1, U10.4
NET_U10_5: C45.2, U10.5
NET_U10_6: C47.1, U10.6
NET_U11_3: U10.14, U11.3
NET_U11_4: U10.13, U11.4
NET_U11_5: U10.17, U11.5
NET_U11_6: U10.16, U11.6
NET_U15_1: C50.1, U15.1
NET_U15_6: R20.2, R21.1, U15.6
NET_U15_8: R19.1, U15.8
NET_U16_3: C55.2, I1.1, U16.3, U16.4
NET_U16_6: C55.1, U16.6
NET_U16_7: C54.1, U16.7, U16.12
NET_U16_10: R24.1, U16.10
NET_U16_11: R22.1, R23.1, U16.11
NET_U16_ATNET_3: I1.2, R23.2
NET_U17_1: R26.1, R27.1, U17.1
NET_U17_3: R28.2, R29.1, U17.3
NET_U17_4: R25.1, U17.4, U20.4, U21.2
NET_U18_1: R2.1, U18.1, U18.2
PROC_I2S1_CK: U1.126, U5.24
PROC_I2S1_SD: U1.123, U5.26
PROC_I2S1_WS: U1.125, U5.23
PROC_SPI1_MISO: U1.42, U2.2
PROC_SPI1_MOSI: U1.43, U2.5
PROC_SPI1_NSS: R10.1, U1.40, U2.1
PROC_SPI1_SCK: U1.41, U2.6
PROC_SYS_JTCK_SWCLK: R15.1, U1.109, U3.4
PROC_SYS_JTDI: R13.1, U1.110, U3.8
PROC_SYS_JTDO_SWO: U1.133, U3.6
PROC_SYS_JTMS_SWDIO: R14.1, U1.105, U3.2
PROC_UART4_CTS: U1.46, U10.8
PROC_UART4_RTS: U1.75, U10.10
PROC_UART4_RX: U1.35, U10.11
PROC_UART4_TX: U1.34, U10.7
RST_OUT_U3_JTAG_RST_B: R12.1, U3.10, U20.1
VCC_S1_7V9: C51.1, C53.1, C58.1, C59.1, J1.1, R19.2, U15.4, U16.15, U16.16
VCC_TIER1_1V2: C37.1, C52.1, R20.1, U5.30, U15.5
VCC_TIER1_3V3: C1.1, C2.1, C3.1, C4.1, C5.1, C6.1, C7.1, C8.1, C9.1, C10.1, C11.1, C12.1, C13.1, C14.1, C15.1, C20.1, C23.1, C24.1, C26.1, C27.1, C29.1, C38.1, C39.1, C42.1, C43.1, C48.1, C49.1, C56.2, C57.1, C60.1, C61.1, F1.2, I1.2, R4.2, R5.2, R6.2, R8.2, R9.2, R10.2, R11.2, R12.2, R13.2, R14.2, R17.2, R23.2, R25.2, R26.2, R28.1, U1.6, U1.17, U1.30, U1.39, U1.52, U1.62, U1.72, U1.84, U1.95, U1.108, U1.121, U1.131, U1.144, U2.8, U3.1, U4.2, U4.8, U5.5, U5.20, U10.12, U10.19, U13.4, U14.4, U16.8, U17.6, U20.5, U21.5
